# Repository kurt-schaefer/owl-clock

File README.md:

# owl-clock
2015 Christmas Project

I built six of these owl clocks in the run up to Christmas 2015.
It uses edge lit acrylic sheets to act as psudo Nixie Tubes. The clock uses an ATMEGA328p at it's core. The display is powered but 40 [WS2812b] (https://www.adafruit.com/datasheets/WS2812B.pdf) RGB leds.
I have a [blog post] (https://retrotechjournal.com/2016/04/04/plexitube-owl-clock/) with a longer write up of the project.

Image
-----------

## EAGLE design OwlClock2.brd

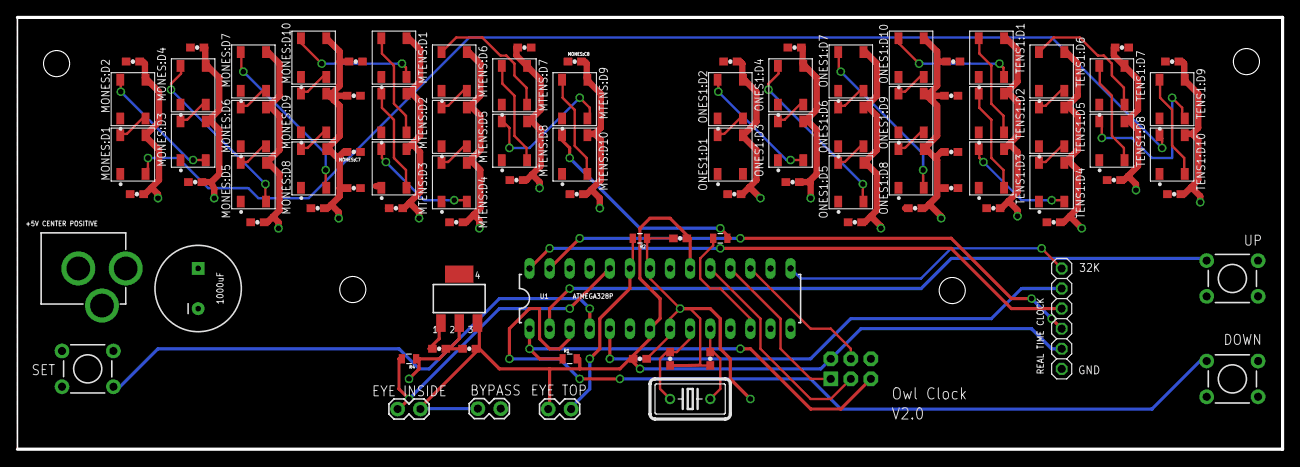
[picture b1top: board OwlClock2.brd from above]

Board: 2 copper layers, 160.0 x 54.6 mm, 99 parts (0 on the bottom side), 59 nets.

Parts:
C1, C2: 22pF; 0603-CAP
C3, C4: 0.1uF; 0603-CAP
C5: 1000uF; CPOL-RADIAL-1000UF-25V
C6, C7: 1uF; 0603-CAP
DOWN: SWITCH-MOMENTARY-2PTH; TACTILE-PTH
IC1: MCP1703DB; SOT223
J1: AVR_SPI_PRG_6NS; 2X3-NS
J2: POWER_JACKPTH; POWER_JACK_PTH
JP1: REAL TIME CLOCK; 1X06
MONES:C1, MONES:C2, MONES:C3, MONES:C4, MONES:C5, MONES:C6, MONES:C7, MONES:C8: 0.1uF; 0603-CAP
MONES:D1, MONES:D2, MONES:D3, MONES:D4, MONES:D5, MONES:D6, MONES:D7, MONES:D8, MONES:D9, MONES:D10: WS2812B
MTENS:C1, MTENS:C2, MTENS:C3, MTENS:C4, MTENS:C5, MTENS:C6, MTENS:C7, MTENS:C8: 0.1uF; 0603-CAP
MTENS:D1, MTENS:D2, MTENS:D3, MTENS:D4, MTENS:D5, MTENS:D6, MTENS:D7, MTENS:D8, MTENS:D9, MTENS:D10: WS2812B
ONES1:C1, ONES1:C2, ONES1:C3, ONES1:C4, ONES1:C5, ONES1:C6, ONES1:C7, ONES1:C8: 0.1uF; 0603-CAP
ONES1:D1, ONES1:D2, ONES1:D3, ONES1:D4, ONES1:D5, ONES1:D6, ONES1:D7, ONES1:D8, ONES1:D9, ONES1:D10: WS2812B
PHOTO_INSIDE: M02LOCK; 1X02_LOCK
PHOTO_TOP: M02LOCK; 1X02_LOCK
Q1: 16Mhz; HC18U-V
R1, R2, R4: 10k; 0805
R3: 470; 0805
SET: SWITCH-MOMENTARY-2PTH; TACTILE-PTH
SUPPLY_BYPASS: M02LOCK; 1X02_LOCK
TENS1:C1, TENS1:C2, TENS1:C3, TENS1:C4, TENS1:C5, TENS1:C6, TENS1:C7, TENS1:C8: 0.1uF; 0603-CAP
TENS1:D1, TENS1:D2, TENS1:D3, TENS1:D4, TENS1:D5, TENS1:D6, TENS1:D7, TENS1:D8, TENS1:D9, TENS1:D10: WS2812B
U1: ATMEGA328P_PDIP; DIL28-3
U$1, U$2, U$3, U$4: STAND-OFF
UP: SWITCH-MOMENTARY-2PTH; TACTILE-PTH

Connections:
32K: JP1.1, U1.15
!RESET: J1.5, R1.1, U1.1
ADC0: PHOTO_TOP.1, R2.2, U1.23
ADC1: PHOTO_INSIDE.1, R4.2, U1.24
DP0: U1.2, UP.1
DP1: DOWN.1, U1.3
DP2: SET.1, U1.4
GND: C1.1, C2.1, C3.2, C4.2, C5.2, C6.1, C7.1, DOWN.3, IC1.2, J1.6, J2.GND, J2.GNDBREAK, JP1.6, MONES:C1.2, MONES:C2.2, MONES:C3.2, MONES:C4.2, MONES:C5.2, MONES:C6.2, MONES:C7.2, MONES:C8.2, MONES:D1.3, MONES:D2.3, MONES:D3.3, MONES:D4.3, MONES:D5.3, MONES:D6.3, MONES:D7.3, MONES:D8.3, MONES:D9.3, MONES:D10.3, MTENS:C1.2, MTENS:C2.2, MTENS:C3.2, MTENS:C4.2, MTENS:C5.2, MTENS:C6.2, MTENS:C7.2, MTENS:C8.2, MTENS:D1.3, MTENS:D2.3, MTENS:D3.3, MTENS:D4.3, MTENS:D5.3, MTENS:D6.3, MTENS:D7.3, MTENS:D8.3, MTENS:D9.3, MTENS:D10.3, ONES1:C1.2, ONES1:C2.2, ONES1:C3.2, ONES1:C4.2, ONES1:C5.2, ONES1:C6.2, ONES1:C7.2, ONES1:C8.2, ONES1:D1.3, ONES1:D2.3, ONES1:D3.3, ONES1:D4.3, ONES1:D5.3, ONES1:D6.3, ONES1:D7.3, ONES1:D8.3, ONES1:D9.3, ONES1:D10.3, R2.1, R4.1, SET.3, TENS1:C1.2, TENS1:C2.2, TENS1:C3.2, TENS1:C4.2, TENS1:C5.2, TENS1:C6.2, TENS1:C7.2, TENS1:C8.2, TENS1:D1.3, TENS1:D2.3, TENS1:D3.3, TENS1:D4.3, TENS1:D5.3, TENS1:D6.3, TENS1:D7.3, TENS1:D8.3, TENS1:D9.3, TENS1:D10.3, U1.8, U1.22, UP.3
MISO: J1.1, U1.18
MONES:N$1: MONES:D2.4, MONES:D3.2
MONES:N$5: MONES:D1.4, MONES:D2.2
MONES:N$6: MONES:D3.4, MONES:D4.2
MONES:N$7: MONES:D4.4, MONES:D5.2
MONES:N$9: MONES:D5.4, MONES:D6.2
MONES:N$10: MONES:D6.4, MONES:D7.2
MONES:N$12: MONES:D7.4, MONES:D8.2
MONES:N$13: MONES:D8.4, MONES:D9.2
MONES:N$15: MONES:D9.4, MONES:D10.2
MOSI: J1.4, U1.17
MTENS:N$1: MTENS:D2.4, MTENS:D3.2
MTENS:N$5: MTENS:D1.4, MTENS:D2.2
MTENS:N$6: MTENS:D3.4, MTENS:D4.2
MTENS:N$7: MTENS:D4.4, MTENS:D5.2
MTENS:N$9: MTENS:D5.4, MTENS:D6.2
MTENS:N$10: MTENS:D6.4, MTENS:D7.2
MTENS:N$12: MTENS:D7.4, MTENS:D8.2
MTENS:N$13: MTENS:D8.4, MTENS:D9.2
MTENS:N$15: MTENS:D9.4, MTENS:D10.2
M_ONES_OUT: MONES:D1.2, TENS1:D10.4
M_TENS_IN: MTENS:D10.4, R3.2
unnamed: MONES:D10.4, MTENS:D1.2
unnamed: R3.1, U1.12
unnamed: ONES1:D10.4, TENS1:D1.2
unnamed: C1.2, Q1.2, U1.9
unnamed: C2.2, Q1.1, U1.10
ONES1:N$1: ONES1:D2.4, ONES1:D3.2
ONES1:N$5: ONES1:D1.4, ONES1:D2.2
ONES1:N$6: ONES1:D3.4, ONES1:D4.2
ONES1:N$7: ONES1:D4.4, ONES1:D5.2
ONES1:N$9: ONES1:D5.4, ONES1:D6.2
ONES1:N$10: ONES1:D6.4, ONES1:D7.2
ONES1:N$12: ONES1:D7.4, ONES1:D8.2
ONES1:N$13: ONES1:D8.4, ONES1:D9.2
ONES1:N$15: ONES1:D9.4, ONES1:D10.2
SCK: J1.3, U1.19
SCL: JP1.3, U1.28
SDA: JP1.4, U1.27
SQW: JP1.2, U1.5
TENS1:N$1: TENS1:D2.4, TENS1:D3.2
TENS1:N$5: TENS1:D1.4, TENS1:D2.2
TENS1:N$6: TENS1:D3.4, TENS1:D4.2
TENS1:N$7: TENS1:D4.4, TENS1:D5.2
TENS1:N$9: TENS1:D5.4, TENS1:D6.2
TENS1:N$10: TENS1:D6.4, TENS1:D7.2
TENS1:N$12: TENS1:D7.4, TENS1:D8.2
TENS1:N$13: TENS1:D8.4, TENS1:D9.2
TENS1:N$15: TENS1:D9.4, TENS1:D10.2
VCC: C5.1, C7.2, IC1.1, J2.PWR, MONES:C1.1, MONES:C2.1, MONES:C3.1, MONES:C4.1, MONES:C5.1, MONES:C6.1, MONES:C7.1, MONES:C8.1, MONES:D1.1, MONES:D2.1, MONES:D3.1, MONES:D4.1, MONES:D5.1, MONES:D6.1, MONES:D7.1, MONES:D8.1, MONES:D9.1, MONES:D10.1, MTENS:C1.1, MTENS:C2.1, MTENS:C3.1, MTENS:C4.1, MTENS:C5.1, MTENS:C6.1, MTENS:C7.1, MTENS:C8.1, MTENS:D1.1, MTENS:D2.1, MTENS:D3.1, MTENS:D4.1, MTENS:D5.1, MTENS:D6.1, MTENS:D7.1, MTENS:D8.1, MTENS:D9.1, MTENS:D10.1, ONES1:C1.1, ONES1:C2.1, ONES1:C3.1, ONES1:C4.1, ONES1:C5.1, ONES1:C6.1, ONES1:C7.1, ONES1:C8.1, ONES1:D1.1, ONES1:D2.1, ONES1:D3.1, ONES1:D4.1, ONES1:D5.1, ONES1:D6.1, ONES1:D7.1, ONES1:D8.1, ONES1:D9.1, ONES1:D10.1, SUPPLY_BYPASS.2, TENS1:C1.1, TENS1:C2.1, TENS1:C3.1, TENS1:C4.1, TENS1:C5.1, TENS1:C6.1, TENS1:C7.1, TENS1:C8.1, TENS1:D1.1, TENS1:D2.1, TENS1:D3.1, TENS1:D4.1, TENS1:D5.1, TENS1:D6.1, TENS1:D7.1, TENS1:D8.1, TENS1:D9.1, TENS1:D10.1
VSS: C3.1, C4.1, C6.2, IC1.3, J1.2, JP1.5, PHOTO_INSIDE.2, PHOTO_TOP.2, R1.2, SUPPLY_BYPASS.1, U1.7, U1.20

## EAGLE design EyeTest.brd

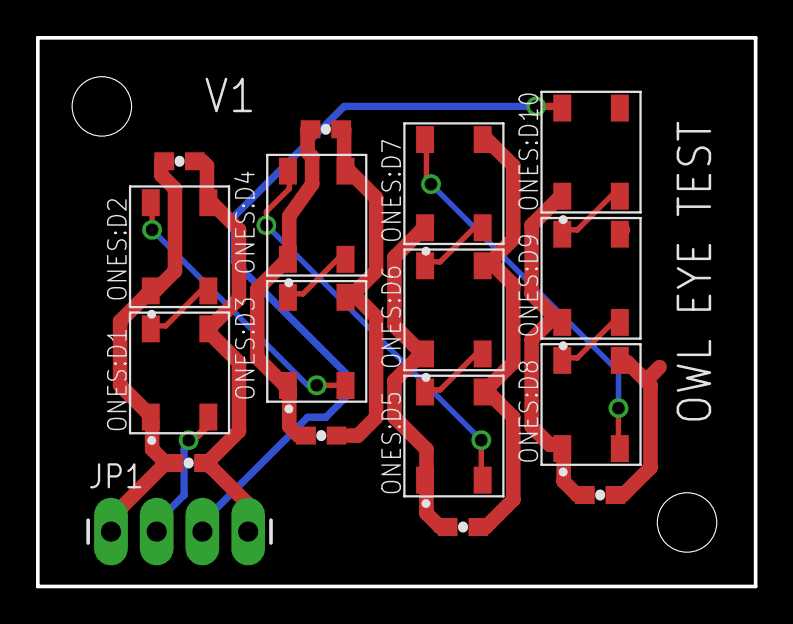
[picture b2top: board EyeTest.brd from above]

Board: 2 copper layers, 39.9 x 30.5 mm, 19 parts (0 on the bottom side), 13 nets.

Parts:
JP1: 1X04_LONGPADS
ONES:C1, ONES:C2, ONES:C3, ONES:C4, ONES:C5, ONES:C6: 0.1uF; 0603-CAP
ONES:D1, ONES:D2, ONES:D3, ONES:D4, ONES:D5, ONES:D6, ONES:D7, ONES:D8, ONES:D9, ONES:D10: WS2812B
U$1, U$2: STAND-OFF

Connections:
DIN: JP1.3, ONES:D10.4
DOUT: JP1.2, ONES:D1.2
GND: JP1.4, ONES:C1.2, ONES:C2.2, ONES:C3.2, ONES:C4.2, ONES:C5.2, ONES:C6.2, ONES:D1.3, ONES:D2.3, ONES:D3.3, ONES:D4.3, ONES:D5.3, ONES:D6.3, ONES:D7.3, ONES:D8.3, ONES:D9.3, ONES:D10.3
ONES:N$1: ONES:D2.4, ONES:D3.2
ONES:N$5: ONES:D1.4, ONES:D2.2
ONES:N$6: ONES:D3.4, ONES:D4.2
ONES:N$7: ONES:D4.4, ONES:D5.2
ONES:N$9: ONES:D5.4, ONES:D6.2
ONES:N$10: ONES:D6.4, ONES:D7.2
ONES:N$12: ONES:D7.4, ONES:D8.2
ONES:N$13: ONES:D8.4, ONES:D9.2
ONES:N$15: ONES:D9.4, ONES:D10.2
VCC: JP1.1, ONES:C1.1, ONES:C2.1, ONES:C3.1, ONES:C4.1, ONES:C5.1, ONES:C6.1, ONES:D1.1, ONES:D2.1, ONES:D3.1, ONES:D4.1, ONES:D5.1, ONES:D6.1, ONES:D7.1, ONES:D8.1, ONES:D9.1, ONES:D10.1

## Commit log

2015-11-19 Very inital version of the schematic. Almost no layout as yet.
2015-11-22 Start work on doing eye layout in a seprate file so I can multi import later.
2015-11-22 Starting to route using the second layer and vias
2015-11-22 After smashing and text adjustment
2015-11-22 Removed the extra caps
2015-11-23 Use Import to make a two eye schematic, add power regulator, basic routing.
2015-11-23 Add vias for led grounds, clean up switches, fix up the supply caps.
2015-11-23 More work on ground plane, fixed ground vias for led power.
2015-11-24 Add power plane fix board outline, finish first pass of routing.
2015-11-24 Finish up labels and cleanup, pass design rules check
2015-11-24 Move Via Stop Limit up to 28mils to tent vias
2015-11-25 Add a tiny test board so I can try reflowing on a smaller board first.
2015-11-25 Fix problem where real time clock was connected to the wrong supply
2015-11-28 Add a simple owl logo illustrator file
2015-11-28 Add owl logo to board, start adding explicit labels to components.
2015-11-29 Inital rework of eye layers and masks to fit board geometry.
2015-11-29 Start work on the led masks
2015-12-03 Add the A double masks for the front of each layer stack.
2015-12-03 Design the backing plate and front plate.
2015-12-06 Add the first very bare bones clock code. This really only loadds the libs, and syncs the RT clock
2015-12-06 Add the led indexing
2015-12-06 Trim out the unused neopixel code and start work on actual clock display.
2015-12-06 Remove unused definitions header.
2015-12-14 Finally add the owlLogo to the boards and add a regulator bypass block.
2016-01-07 More work on the body.
2016-01-14 A lot more work on the owl body. Updated curves, ab bc cd da masks
2016-01-21 The very basic first just showing the time clock code
2016-01-30 Basic moon function for clock.
2016-02-01 Fix 24 hour to 12 hour clock conversion.
2016-02-16 Start to package up the astromomical calculations as libraries.
2016-02-16 This packages up the astronomical calculations for the moon/sun into a library that uses the float64 lib.
2016-02-18 Add holiday dates and easter calculation to the basic libs.
2016-02-18 Remove duplicate day/month defines
2016-02-18 Further work to compute holidays, I am however discovering that there is not enough program space to compute the solar events, which also means no sunrise/set times, moon rise/set times, etc. So SAD
2016-02-18 Add a RLE version of storing the solar events for the next 100 years. This should be replaced with a direct access 4 values per byte direct packing next.
2016-02-21 Convert to different solar event packing scheme.
2016-02-25 Take a first stab at clock setting with auto repeat. Add a define for testing on an UNO with serial printing.
2016-02-25 Make it so during setting we show 12 hours and a PM indicator.
2016-02-27 Add moon and sun indicators when setting the month/day. Swap up/down to be more intuitive. Adjust color pulsing.
2016-02-28 Fix time setting so it doen't mess up the year.
2016-02-28 update the ramping code a little, and fix up the eeprom saving stuff. Now the setting code fully works.
2016-02-28 Convert away from using float64 computation for the moon. This shrinks the code back down to 17k
2016-02-28 Switch to direct indexing of he special characters.
2016-02-28 Add eye looking around code right now it has a green background
2016-02-28 Add the spinning globe effect
2016-02-28 Add the golden spinning ring effect
2016-03-03 Add gaussian random flicker to eye, bump autorepeat delay out a little again.
2016-03-03 Convert to global brightness/color for digits. Add Blue White and Red flag wave animation.
2016-03-10 Add birthday and holiday event infrastructure. Work on countdown still in progress.
2016-03-14 Add basic room brightness tracking, and the rest of the birthday colors. Also start work on firworks.
2016-03-14 Add very basic halloween flames and make the green eye not flicker.
2016-03-14 Rewrite the fireworks. Adjust the dimming spring constant a bit.
2016-03-14 Add temperature display and annaversary
2016-03-14 Add auto daylight savings time support, but at midnight not 2am
2016-03-16 Add Optical Theremin
2016-03-17 Add easter egg where multi colored eeggs appear in the background on easter.
2016-03-18 Add April Fools sillyness
2016-03-18 Meaningless change
2016-03-18 Fix the temperature output to show deg F.
2016-03-19 Adjust colors for temps, this is the version that M&D have currently
2016-03-19 Fix eeprom reading/writing bug and remove exta smarts about adjusting gmt automatically if you change the hour buy one, also fix issue where incorrect hour could be shown as you change hours during t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
2016-04-03 I have no idea about license stuff but I'll put this up here for now.
2016-04-03 Hook a picture up to the README
2016-04-03 Remove the old out of date OwlClock.brd/.sch
2016-04-06 Put a link to my blog in the readme
2016-09-03 Respond to request to put this under cern open hardware license.

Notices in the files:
parts and their libraries:
SparkFun-Capacitors: Licensing: Creative Commons ShareAlike 4.0 International - https://creativecommons.org/licenses/by-sa/4.0
